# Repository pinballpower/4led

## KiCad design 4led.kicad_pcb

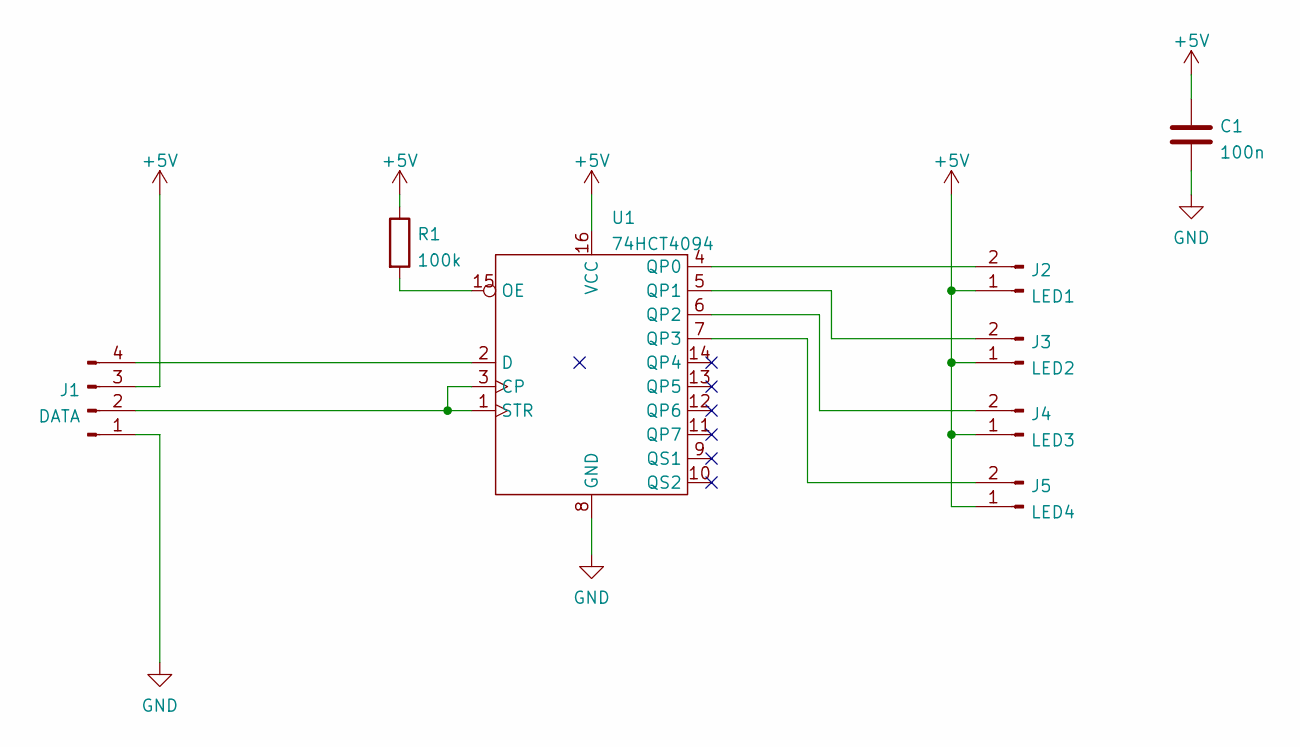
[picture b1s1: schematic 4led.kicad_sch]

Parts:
C1: 100n; C_Disc_D3.0mm_W1.6mm_P2.50mm
J1: DATA; Molex_KK-254_AE-6410-04A_1x04_P2.54mm_Vertical
J2: LED1; Molex_KK-254_AE-6410-02A_1x02_P2.54mm_Vertical
J3: LED2; Molex_KK-254_AE-6410-02A_1x02_P2.54mm_Vertical
J4: LED3; Molex_KK-254_AE-6410-02A_1x02_P2.54mm_Vertical
J5: LED4; Molex_KK-254_AE-6410-02A_1x02_P2.54mm_Vertical
R1: 100k; R_Axial_DIN0204_L3.6mm_D1.6mm_P7.62mm_Horizontal
U1: 74HCT4094; DIP-16_W7.62mm_LongPads

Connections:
+5V: C1.1, J1.3, J2.1, J3.1, J4.1, J5.1, R1.1, U1.16 (VCC)
GND: C1.2, J1.1, U1.8 (GND)
unnamed: J1.2, U1.1 (STR), U1.3 (CP)
unnamed: J1.4, U1.2 (D)
unnamed: J2.2, U1.4 (QP0)
unnamed: J3.2, U1.5 (QP1)
unnamed: J4.2, U1.6 (QP2)
unnamed: J5.2, U1.7 (QP3)
unnamed: R1.2, U1.15 (OE)

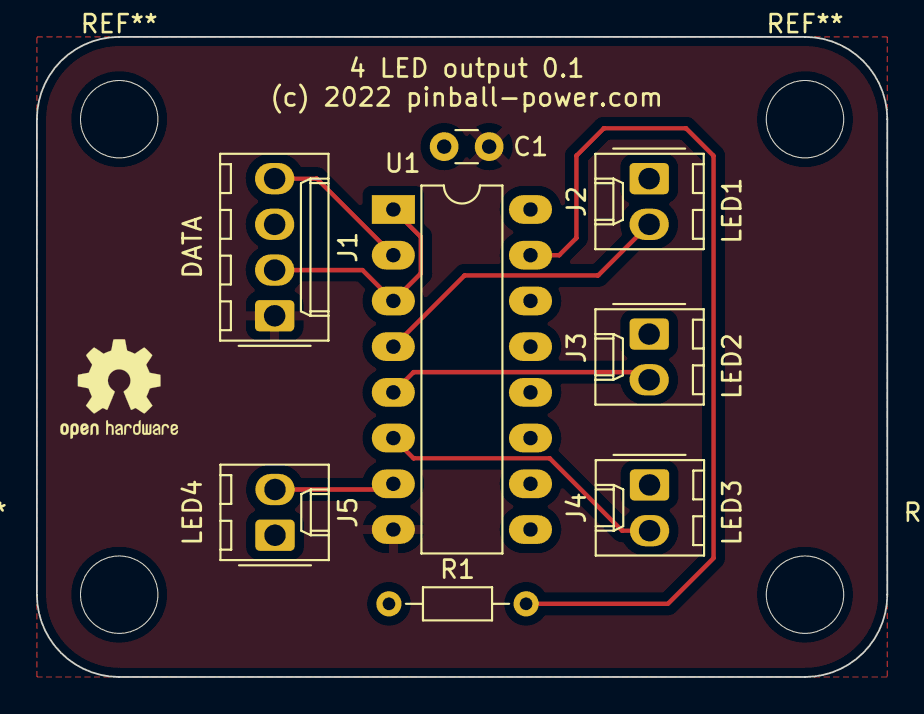
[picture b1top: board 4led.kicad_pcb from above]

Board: 2 copper layers, 47.2 x 35.6 mm, 8 parts (0 on the bottom side), 9 nets.

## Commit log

2022-01-30 Initial version

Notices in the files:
4led.kicad_pcb:
(c) 2022 pinball-power.com
